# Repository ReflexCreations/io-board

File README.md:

# RE:Flex Dance I/O v2 PCB Design 

This repository contains source documents and manufacturing files for the RE:Flex Dance Pad's I/O Board. It was created using [KiCAD 5.1.4](https://kicad.org/).

The I/O Boards purpose is to provide an interface between a computer (using USB 2.0) and 4 'panel boards' (using RJ45) to:
- Receive panel board pressure sensor data, organize the data and send it to computer programs
- Receive LED data from computer programs, organize and send it to panel boards to display on RGB LED array

## Getting your own

The least-work way is to order the Printed Circuit board (PCB) assembled from JLCPCB. You can also order a bare board from any PCB prototyping place, and then source and solder all the components yourself.
Board: The JLCPCB assembled route
1. Grab the latest PCB manufacturing files

    Go to the Latest release and download `release-v2-RC2.zip`. This contains all the PCB fabrication outputs from KiCAD. Alternatively, clone or download this repository, open the project from the pcb/multi-midi folder in KiCad and export the gerber files yourself.
    
    If you want, you can generate the manufacture files yourself, but this is trickier than generating the gerber files since a 3rd party script needs to be installed, and output files manually edited to work with JLCPCB. Documentation: How to generate the BOM and Centroid file from KiCAD

2. Place the order with [JLCPCB](https://jlcpcb.com)
```
    Click "Add your gerber file", select the release-v2-RC2.zip file from the releases.
    Pick a board color or leave it at the default green. Last time I checked different colors only affect build time, not price.
    Pick a surface finish or leave it on the default. The default is cheapest, but contains lead. ENIG gives the pads a nice golden finish instead of silver.
    Leave all the other options as they are.
    Scroll down to "SMT Assembly" and switch it on
    Select "assemble top side"
    Pick a quantity; if you only want one, 2 will be the minimum here
    Click "Confirm".
    On the right side of the page, click "Next"
    Click "Add BOM File"; upload the *release/bom.csv* file
    Click "Add CPL File"; upload the the *release/io-board-top-pos.csv* file
    Click "Next"
    Review the specified parts; they should all be "confirmed" in the right column, so you can leave everything as it is.
    Click "Next"
    In the preview, some ICs might look like they're oriented wrong. This is a problem with their viewer; the files are correct. If it ends up wrong (not aligning with the pads), they'll either correct it or email you to find a solution.
    Click "Save to cart"
    Click "Check out Securely"
    Add your shipping and billing details
    Select a shipping method. Usually the DHL-based ones are fine. You can gamble on whether or not you want duty and customs paid up front (more expensive), or hope for the best with the cheaper option, in which case you might get a bill from the courier later.
    Click "Continue" when you're happy
    Click "submit order"
    Do what you need to do for payment
    Wait for your boards to get delivered
```

3. Order the remaining through-hole parts - A list of these parts can be seen at `release/unpopulated.csv`. Companies that sell parts like this include Mouser, Digikey, RS-Components and Farnell.

4. Solder the remaining parts onto the board. Fairly evident where each of them go, though a more detailed guide here could be helpful. Pull requests welcome. :-)

## Future Improvements
- Currently, there's a lot of connectors. We could daisy chain a number of boards if we utilized the correct UART transmission protocol. My hope is eventually to just have 3 RJ45 connectors, which can each address a maximum of 3 panels.
- We could also eliminate the need for all of the output DC power jacks by running power along the RJ45 cable, similar to 'Power over Ethernet'. This would probably depend on using lower-powered LEDs, which is already an improvement listed under the panel board.
- The RS-485 transceivers probably don't need direction-switching, and the transceiver is entirely deprecated connected to the USART clock lines. We could save some microcontroller pins by removing this. This'd also make firmware updates to panel boards over UART a lot easier.
- More output types! Currently we just have USB. In the future, we could connect to arcade machines, consoles, and other things. 
- More methods of panel addressing. Currently the RJ45 method is the only way. So any future panel boards would have to conform to that specification. Some people may just want a much easier method of addressing digital sensors or force sensitive resistors. This could be supported on the I/O board to reduce requirements for travel pads and the likes.
- Easier debugging. The status LEDs are ambiguous as to what they do. More status LEDs, more text indication on the board (e.g. 'Left Panel Unconnected' next to a status LED) could make things a lot easier for the end user.
- Future form factor updates. People might want to use these boards in an arcade pad. They may want to avoid the aluminium extrusion framework. Fitting this board for all sorts of different requirements will improve accessibility to the electronics.
- These boards could have through hole parts populated by a batch manufacturer, and be sold without the need for soldering. If you'd like to sell these boards, please get in touch, and we can help you source finished boards.

## Firmware

For the board to function, you will need to install the I/O board firmware to it. You can find this information within the repo for the IO-Firmware.

## License

For license details, see LICENSE file

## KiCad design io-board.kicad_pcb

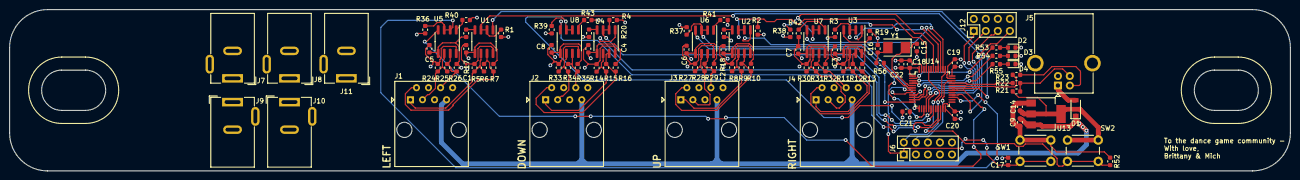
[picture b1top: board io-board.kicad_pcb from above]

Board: 4 copper layers, 270.0 x 34.0 mm, 95 parts (0 on the bottom side), 67 nets.

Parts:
C1, C2, C3, C4, C5, C6, C7, C8, C17, C18, C19, C20, C21: 0.1u; C_0603_1608Metric
C9: 22u; C_0603_1608Metric
C14: 10u; C_0603_1608Metric
C15, C16: 22p; C_0603_1608Metric
C22: 1u; C_0603_1608Metric
D1: D_Schottky; D_SOD-123
D2, D3, D4: LED; LED_0603_1608Metric
J1, J2, J3, J4: RJ45; RJ45_Amphenol_54602-x08_Horizontal
J5: USB_B; USB_B_OST_USB-B1HSxx_Horizontal
J6: Conn_02x05_Odd_Even; PinHeader_2x05_P2.54mm_Vertical
J7, J8, J9, J10, J11: Barrel_Jack_MountingPin; BarrelJack_Wuerth_6941xx301002
J12: Conn_02x04_Odd_Even; PinHeader_2x04_P2.54mm_Vertical
R1, R2, R3, R4, R17, R18, R19, R20, R36, R37, R38, R39, R40, R41, R42, R43, R52: 10k; R_0603_1608Metric
R5, R7, R8, R10, R11, R13, R14, R16, R24, R26, R27, R29, R30, R32, R33, R35: 360R; R_0603_1608Metric
R6, R9, R12, R15, R25, R28, R31, R34: 100R; R_0603_1608Metric
R21: 1.5k; R_0603_1608Metric
R22, R23: 22R; R_0603_1608Metric
R53, R54, R55: 270R; R_0603_1608Metric
R56: 220R; R_0603_1608Metric
SW1, SW2: SW_Push; SW_PUSH_6mm
U1, U2, U3, U4, U5, U6, U7, U8: SP3485EN; SOIC-8_3.9x4.9mm_P1.27mm
U13: AMS1117-3.3; SOT-223-3_TabPin2
U14: STM32F303CCTx; LQFP-48_7x7mm_P0.5mm
Y1: 8MHz; Crystal_SMD_5032-2Pin_5.0x3.2mm

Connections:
+3V3: C1.1, C2.1, C3.1, C4.1, C5.1, C6.1, C7.1, C8.1, C14.1, C18.1, C19.1, C20.1, C21.1, C22.1, J6.7, J6.8, R5.1, R8.1, R11.1, R14.1, R21.2, R24.1, R27.1, R30.1, R33.1, R40.1, R41.1, R42.1, R43.1, SW2.1, U1.8 (VCC), U2.8 (VCC), U3.8 (VCC), U4.8 (VCC), U5.8 (VCC), U6.8 (VCC), U7.8 (VCC), U8.8 (VCC), U13.2 (VO), U14.1 (VBAT), U14.9 (VDDA), U14.24 (VDD), U14.36 (VDD), U14.48 (VDD)
+5V: C9.1, D1.1 (K), J1.7, J2.7, J3.7, J4.7, U13.3 (VI)
+24V: J7.1, J8.1, J9.1, J10.1, J11.1
GND: C1.2, C2.2, C3.2, C4.2, C5.2, C6.2, C7.2, C8.2, C9.2, C14.2, C15.1, C16.2, C17.2, C18.2, C19.2, C20.2, C21.2, C22.2, D2.1 (K), D3.1 (K), D4.1 (K), J1.8, J2.8, J3.8, J4.8, J5.4 (GND), J5.5 (Shield), J6.5, J6.6, J12.2, J12.4, J12.6, J12.8, R1.2, R2.2, R3.2, R4.2, R7.2, R10.2, R13.2, R16.2, R17.2, R18.2, R19.2, R20.2, R26.2, R29.2, R32.2, R35.2, R36.2, R37.2, R38.2, R39.2, R52.1, SW1.1, U1.5 (GND), U2.5 (GND), U3.5 (GND), U4.5 (GND), U5.5 (GND), U6.5 (GND), U7.5 (GND), U8.5 (GND), U13.1 (GND), U14.8 (VSSA), U14.23 (VSS), U14.35 (VSS), U14.47 (VSS)
GNDD: J7.2, J8.2, J9.2, J10.2, J11.2
NRST: C17.1, J6.1, SW1.2, U14.7 (NRST)
unnamed: C15.2, U14.5 (PF0), Y1.1
unnamed: C16.1, R56.1, Y1.2
unnamed: D1.2 (A), J5.1 (VBUS)
unnamed: D2.2 (A), R53.1
unnamed: D3.2 (A), R54.1
unnamed: D4.2 (A), R55.1
unnamed: J5.2 (D-), R23.1
unnamed: J5.3 (D+), R21.1, R22.1
unnamed: J12.1, U14.10 (PA0)
unnamed: J12.3, U14.11 (PA1)
unnamed: J12.5, U14.16 (PA6)
unnamed: J12.7, U14.17 (PA7)
unnamed: R17.1, U1.4 (DI)
unnamed: R18.1, U2.4 (DI)
unnamed: R19.1, U3.4 (DI)
unnamed: R20.1, U4.4 (DI)
unnamed: R40.2, U5.1 (RO)
unnamed: R41.2, U6.1 (RO)
unnamed: R42.2, U7.1 (RO)
unnamed: R43.2, U8.1 (RO)
unnamed: R52.2, SW2.2, U14.44 (BOOT0)
unnamed: R53.2, U14.2 (PC13)
unnamed: R54.2, U14.3 (PC14)
unnamed: R55.2, U14.4 (PC15)
unnamed: R56.2, U14.6 (PF1)
SWCLK: J6.2, U14.37 (PA14)
SWDIO: J6.4, U14.34 (PA13)
USART1_RX: U1.1 (RO), U14.31 (PA10)
USART1_RX+: J1.1, R5.2, R6.1, U1.6 (A)
USART1_RX-: J1.2, R6.2, R7.1, U1.7 (B)
USART1_RX_DR: R1.1, U1.2 (~RE), U1.3 (DE), U14.28 (PB15)
USART1_TX: U5.4 (DI), U14.30 (PA9)
USART1_TX+: J1.3, R24.2, R25.1, U5.6 (A)
USART1_TX-: J1.6, R25.2, R26.1, U5.7 (B)
USART1_TX_DR: R36.1, U5.2 (~RE), U5.3 (DE), U14.27 (PB14)
USART2_RX0: U2.1 (RO), U14.13 (PA3)
USART2_RX0+: J3.1, R8.2, R9.1, U2.6 (A)
USART2_RX0-: J3.2, R9.2, R10.1, U2.7 (B)
USART2_RX0_DR: R2.1, U2.2 (~RE), U2.3 (DE), U14.45 (PB8)
USART2_RX1: U3.1 (RO), U14.38 (PA15)
USART2_RX1+: J4.1, R11.2, R12.1, U3.6 (A)
USART2_RX1-: J4.2, R12.2, R13.1, U3.7 (B)
USART2_RX1_DR: R3.1, U3.2 (~RE), U3.3 (DE), U14.40 (PB4)
USART2_TX0: U6.4 (DI), U14.12 (PA2)
USART2_TX0+: J3.3, R27.2, R28.1, U6.6 (A)
USART2_TX0-: J3.6, R28.2, R29.1, U6.7 (B)
USART2_TX0_DR: R37.1, U6.2 (~RE), U6.3 (DE), U14.15 (PA5)
USART2_TX1: U7.4 (DI), U14.39 (PB3)
USART2_TX1+: J4.3, R30.2, R31.1, U7.6 (A)
USART2_TX1-: J4.6, R31.2, R32.1, U7.7 (B)
USART2_TX1_DR: R38.1, U7.2 (~RE), U7.3 (DE), U14.42 (PB6)
USART3_RX: U4.1 (RO), U14.22 (PB11)
USART3_RX+: J2.1, R14.2, R15.1, U4.6 (A)
USART3_RX-: J2.2, R15.2, R16.1, U4.7 (B)
USART3_RX_DR: R4.1, U4.2 (~RE), U4.3 (DE), U14.19 (PB1)
USART3_TX: U8.4 (DI), U14.21 (PB10)
USART3_TX+: J2.3, R33.2, R34.1, U8.6 (A)
USART3_TX-: J2.6, R34.2, R35.1, U8.7 (B)
USART3_TX_DR: R39.1, U8.2 (~RE), U8.3 (DE), U14.18 (PB0)
USB_D+: R22.2, U14.33 (PA12)
USB_D-: R23.2, U14.32 (PA11)

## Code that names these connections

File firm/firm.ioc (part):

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Mcu.Name=STM32F303C(B-C)Tx
Mcu.Package=LQFP48
Mcu.UserName=STM32F303CCTx
PA0.Signal=GPIO_Output
PA1.Signal=GPIO_Output
PA10.Mode=Synchronous
PA10.Signal=USART1_RX
PA11.Mode=Device
PA11.Signal=USB_DM
PA12.Mode=Device
PA12.Signal=USB_DP
PA13.Mode=Serial_Wire
PA13.Signal=SYS_JTMS-SWDIO
PA14.Mode=Serial_Wire
PA14.Signal=SYS_JTCK-SWCLK
PA15.Signal=EVENTOUT
PA2.Mode=Synchronous
PA2.Signal=USART2_TX
PA3.Mode=Synchronous
PA3.Signal=USART2_RX
PA4.Mode=Synchronous
PA4.Signal=USART2_CK
PA5.Signal=GPIO_Output
PA6.Signal=GPIO_Output
PA7.Signal=GPIO_Output
PA8.Mode=Synchronous
PA8.Signal=USART1_CK
PA9.Mode=Synchronous
PA9.Signal=USART1_TX
PB0.Signal=GPIO_Output
PB1.Signal=GPIO_Output
PB10.Mode=Synchronous
PB10.Signal=USART3_TX
PB11.Mode=Synchronous
PB11.Signal=USART3_RX
PB12.Mode=Synchronous
PB12.Signal=USART3_CK
PB13.Signal=GPIO_Output
PB14.Signal=GPIO_Output
PB15.Signal=GPIO_Output
PB2.Signal=GPIO_Output
PB3.Signal=EVENTOUT
PB4.Signal=GPIO_Output
PB5.Signal=EVENTOUT
PB6.Signal=GPIO_Output
PB7.Signal=GPIO_Output
PB8.Signal=GPIO_Output
PB9.Signal=GPIO_Output
PC13.Signal=GPIO_Output
PC14-OSC32_IN.Signal=GPIO_Output
PC15-OSC32_OUT.Signal=GPIO_Output
PF0-OSC_IN.Mode=HSE-External-Oscillator
PF0-OSC_IN.Signal=RCC_OSC_IN
PF1-OSC_OUT.Mode=HSE-External-Oscillator
PF1-OSC_OUT.Signal=RCC_OSC_OUT
RCC.HSEPLLFreq_Value=8000000
RCC.HSE_VALUE=8000000
RCC.SYSCLKFreq_VALUE=8000000
board=custom

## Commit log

2020-09-13 First schematic, pending review
2020-09-16 Order in
2020-10-18 Stage for release v2.0
2020-11-07 Safe margins for no standoffs
2020-12-12 Readme update
2021-11-08 Update README.md
    https://forum.kicad.info/t/warning-avoid-all-links-to-kicad-pcb-org-use-kicad-org/31521
2024-07-24 Schem for RS485 circuit corrections
2024-07-26 RS-485 transceiver fixes - production
